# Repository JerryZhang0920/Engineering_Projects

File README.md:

# Engineering Projects

:electric_plug: This repository has all the projects I made for my engineering class

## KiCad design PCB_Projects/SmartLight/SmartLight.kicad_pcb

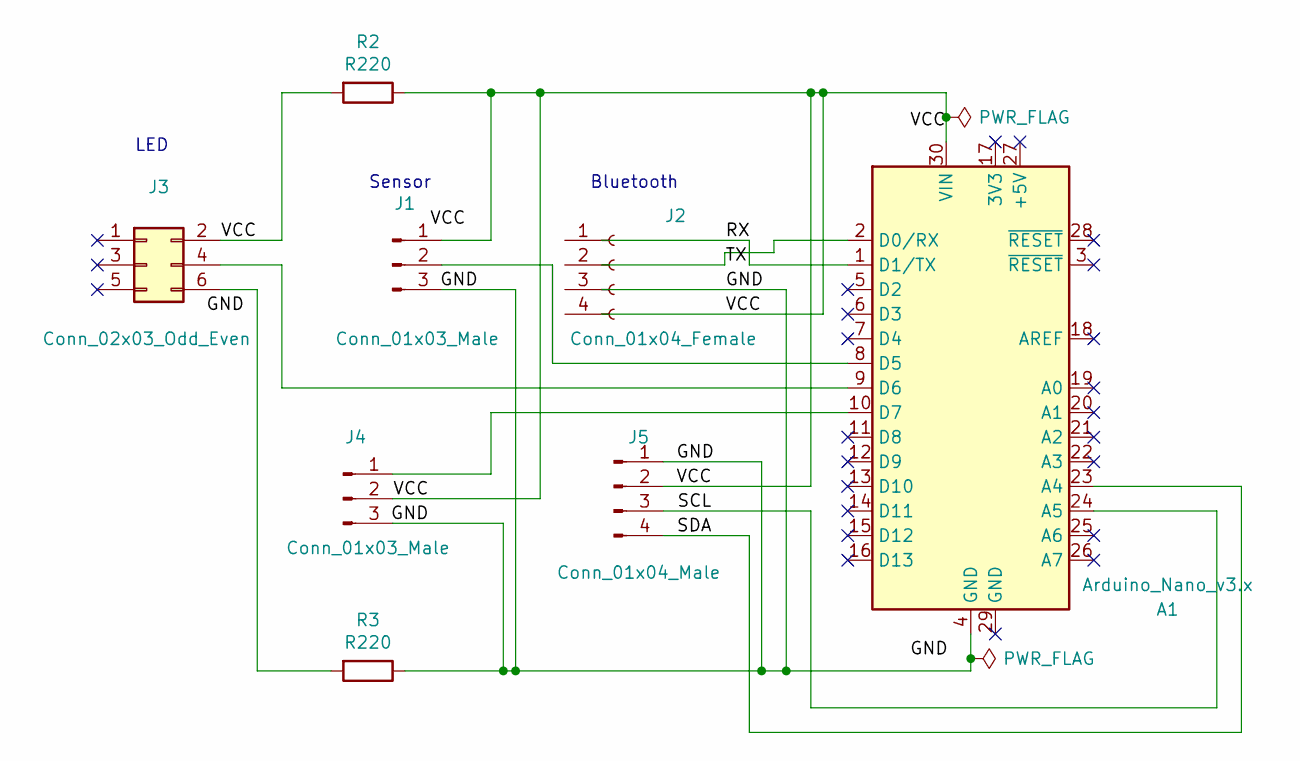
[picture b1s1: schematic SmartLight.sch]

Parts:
A1: Arduino_Nano_v3.x; Arduino_Nano
J1, J4: Conn_01x03_Male; PinHeader_1x03_P2.54mm_Vertical
J2: Conn_01x04_Female; PinSocket_1x04_P2.54mm_Vertical
J3: Conn_02x03_Odd_Even; PinHeader_2x03_P2.54mm_Vertical
J5: Conn_01x04_Male; PinHeader_1x04_P2.54mm_Vertical
R2, R3: R220; R_1206_3216Metric_Pad1.30x1.75mm_HandSolder

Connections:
/GND: A1.4 (GND), J1.3, J4.3, J5.1, R3.1
/RX: A1.1 (D1/TX)
/SCL: A1.24 (A5), J5.3
/SDA: A1.23 (A4), J5.4
/TX: A1.2 (D0/RX)
/VCC: A1.30 (VIN), J1.1, J3.2, J4.2, J5.2, R2.1, R2.2
unnamed: A1.8 (D5), J1.2
unnamed: A1.9 (D6), J3.4
unnamed: A1.10 (D7), J4.1
unnamed: J3.6, R3.2

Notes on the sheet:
Bluetooth
Sensor
LED

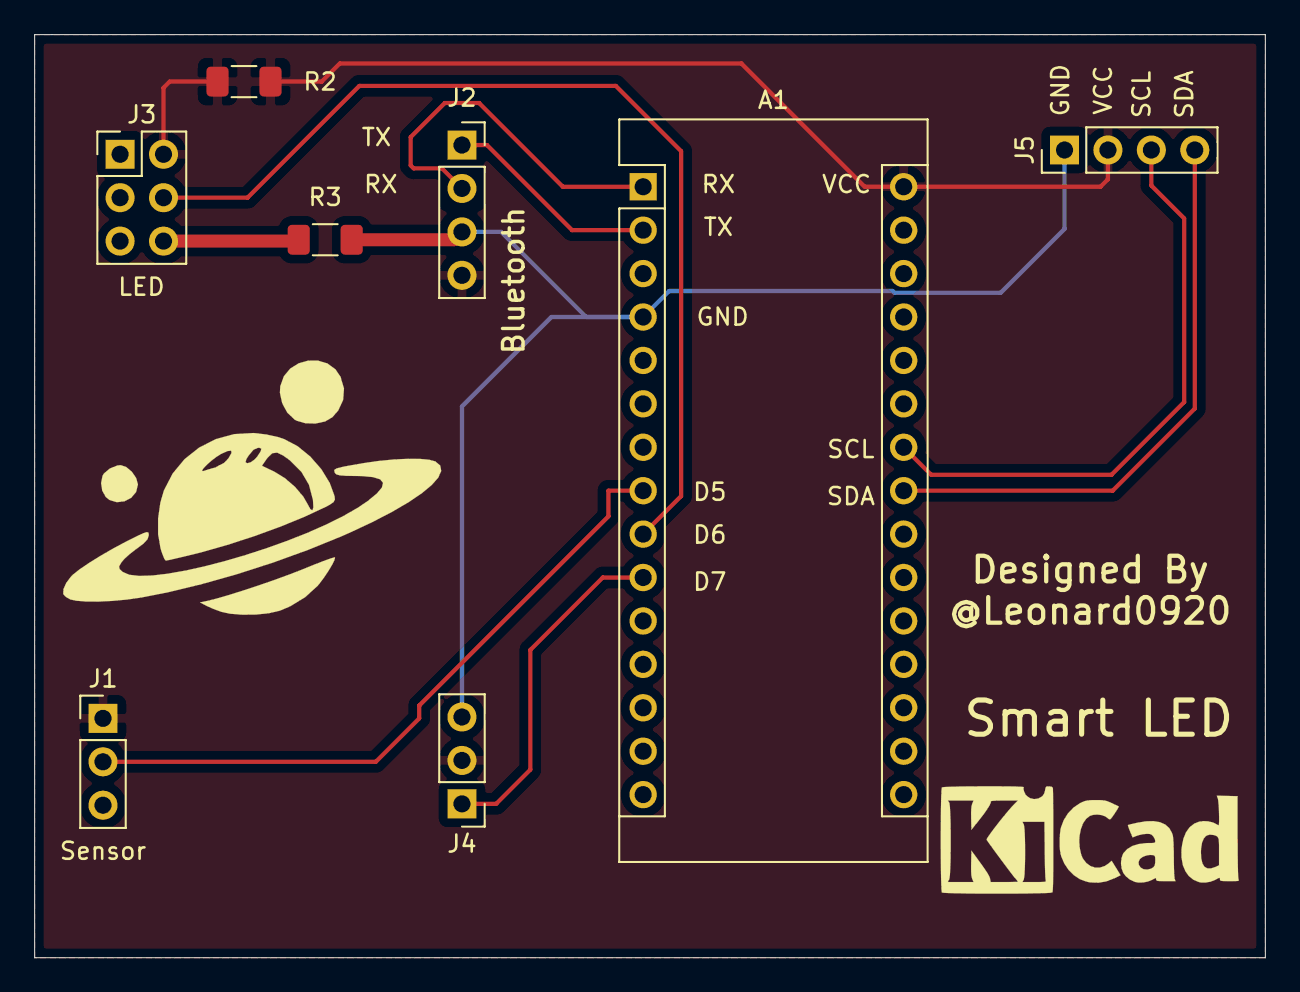
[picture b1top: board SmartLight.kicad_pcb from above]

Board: 2 copper layers, 72.0 x 54.0 mm, 8 parts (0 on the bottom side), 8 nets.

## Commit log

2021-02-01 Create Smart LED
